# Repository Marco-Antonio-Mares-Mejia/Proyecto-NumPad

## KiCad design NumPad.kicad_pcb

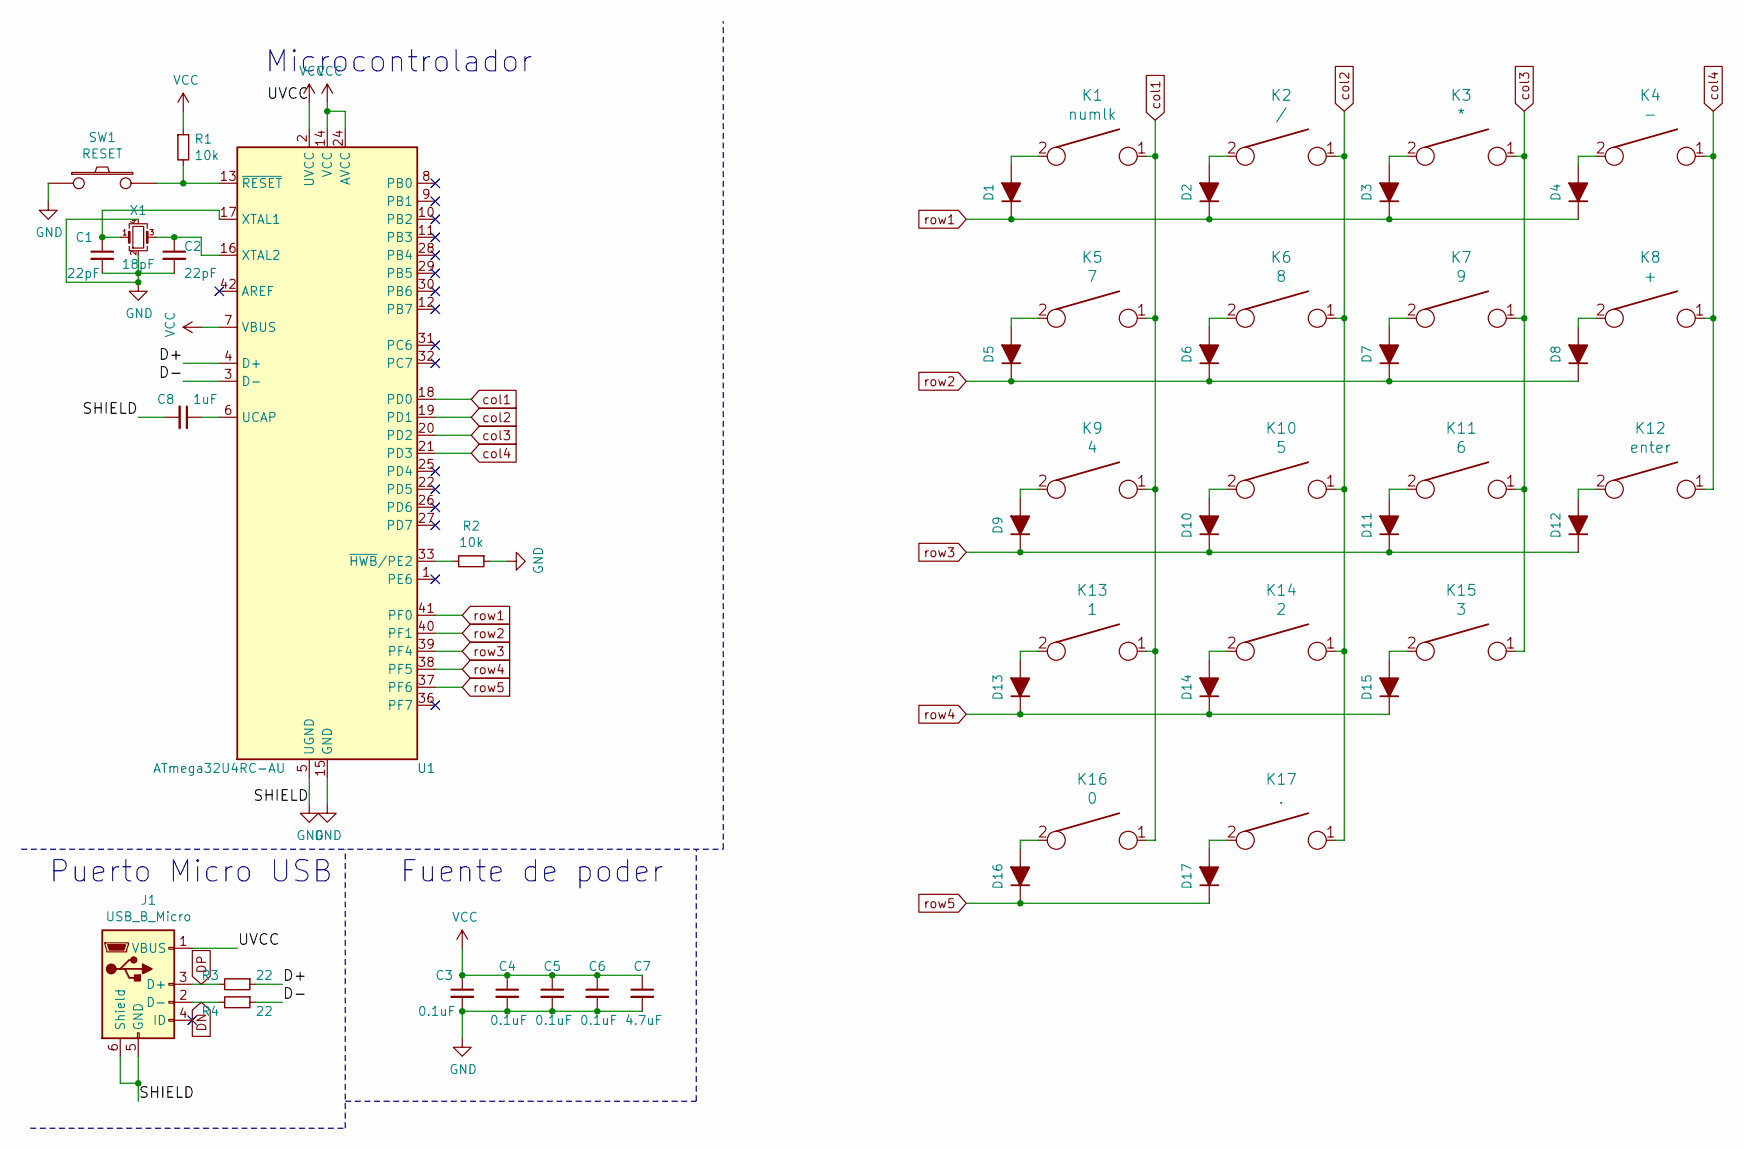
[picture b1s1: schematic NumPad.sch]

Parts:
C1, C2: 22pF; C_0805_2012Metric
C3, C4, C5, C6: 0.1uF; C_0805_2012Metric
C7: 4.7uF; C_0805_2012Metric
C8: 1uF; C_0805_2012Metric
D1, D2, D3, D4, D5, D6, D7, D8, D9, D10, D11, D12, D13, D14, D15, D16, D17: D_ALT; D_SOD-123
J1: USB_B_Micro; USB_microB
K1: numlk; SW_Cherry_MX_1.00u_PCB
K2: /; SW_Cherry_MX_1.00u_PCB
K3: *; SW_Cherry_MX_1.00u_PCB
K4: -; SW_Cherry_MX_1.00u_PCB
K5: 7; SW_Cherry_MX_1.00u_PCB
K6: 8; SW_Cherry_MX_1.00u_PCB
K7: 9; SW_Cherry_MX_1.00u_PCB
K8: +; SW_Cherry_MX_2.00u_Vertical_PCB
K9: 4; SW_Cherry_MX_1.00u_PCB
K10: 5; SW_Cherry_MX_1.00u_PCB
K11: 6; SW_Cherry_MX_1.00u_PCB
K12: enter; SW_Cherry_MX_2.00u_Vertical_PCB
K13: 1; SW_Cherry_MX_1.00u_PCB
K14: 2; SW_Cherry_MX_1.00u_PCB
K15: 3; SW_Cherry_MX_1.00u_PCB
K16: 0; SW_Cherry_MX_2.00u_PCB
K17: .; SW_Cherry_MX_1.00u_PCB
R1, R2: 10k; R_0805_2012Metric
R3, R4: 22; R_0603_1608Metric
SW1: RESET; SW_PUSH_6mm
U1: ATmega32U4RC-AU; TQFP-44_10x10mm_P0.8mm
X1: 18pF; Crystal_SMD_SeikoEpson_FA238-4Pin_3.2x2.5mm

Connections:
/D+: R3.1, U1.4 (D+)
/D-: R4.1, U1.3 (D-)
DN: J1.2 (D-), R4.2
DP: J1.3 (D+), R3.2
GND: C1.2, C2.2, C3.2, C4.2, C5.2, C6.2, C7.2, C8.2, J1.5 (GND), J1.6 (Shield), R2.1, SW1.1, U1.5 (UGND), U1.15 (GND), U1.23 (GND), U1.35 (GND), U1.43 (GND), X1.2, X1.4
unnamed: C1.1, U1.17 (XTAL1), X1.1
unnamed: C2.1, U1.16 (XTAL2), X1.3
unnamed: C8.1, U1.6 (UCAP)
unnamed: D1.2 (A), K1.2
unnamed: D2.2 (A), K2.2
unnamed: D3.2 (A), K3.2
unnamed: D4.2 (A), K4.2
unnamed: D5.2 (A), K5.2
unnamed: D6.2 (A), K6.2
unnamed: D7.2 (A), K7.2
unnamed: D8.2 (A), K8.2
unnamed: D9.2 (A), K9.2
unnamed: D10.2 (A), K10.2
unnamed: D11.2 (A), K11.2
unnamed: D12.2 (A), K12.2
unnamed: D13.2 (A), K13.2
unnamed: D14.2 (A), K14.2
unnamed: D15.2 (A), K15.2
unnamed: D16.2 (A), K16.2
unnamed: D17.2 (A), K17.2
unnamed: R1.2, SW1.2, U1.13 (~RESET)
unnamed: R2.2, U1.33 (~HWB~/PE2)
VCC: C3.1, C4.1, C5.1, C6.1, C7.1, J1.1 (VBUS), R1.1, U1.2 (UVCC), U1.7 (VBUS), U1.14 (VCC), U1.24 (AVCC), U1.34 (VCC), U1.44 (AVCC)
col1: K1.1, K5.1, K9.1, K13.1, K16.1, U1.18 (PD0)
col2: K2.1, K6.1, K10.1, K14.1, K17.1, U1.19 (PD1)
col3: K3.1, K7.1, K11.1, K15.1, U1.20 (PD2)
col4: K4.1, K8.1, K12.1, U1.21 (PD3)
row1: D1.1 (K), D2.1 (K), D3.1 (K), D4.1 (K), U1.41 (PF0)
row2: D5.1 (K), D6.1 (K), D7.1 (K), D8.1 (K), U1.40 (PF1)
row3: D9.1 (K), D10.1 (K), D11.1 (K), D12.1 (K), U1.39 (PF4)
row4: D13.1 (K), D14.1 (K), D15.1 (K), U1.38 (PF5)
row5: D16.1 (K), D17.1 (K), U1.37 (PF6)

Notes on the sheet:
Microcontrolador
Fuente de poder
Puerto Micro USB

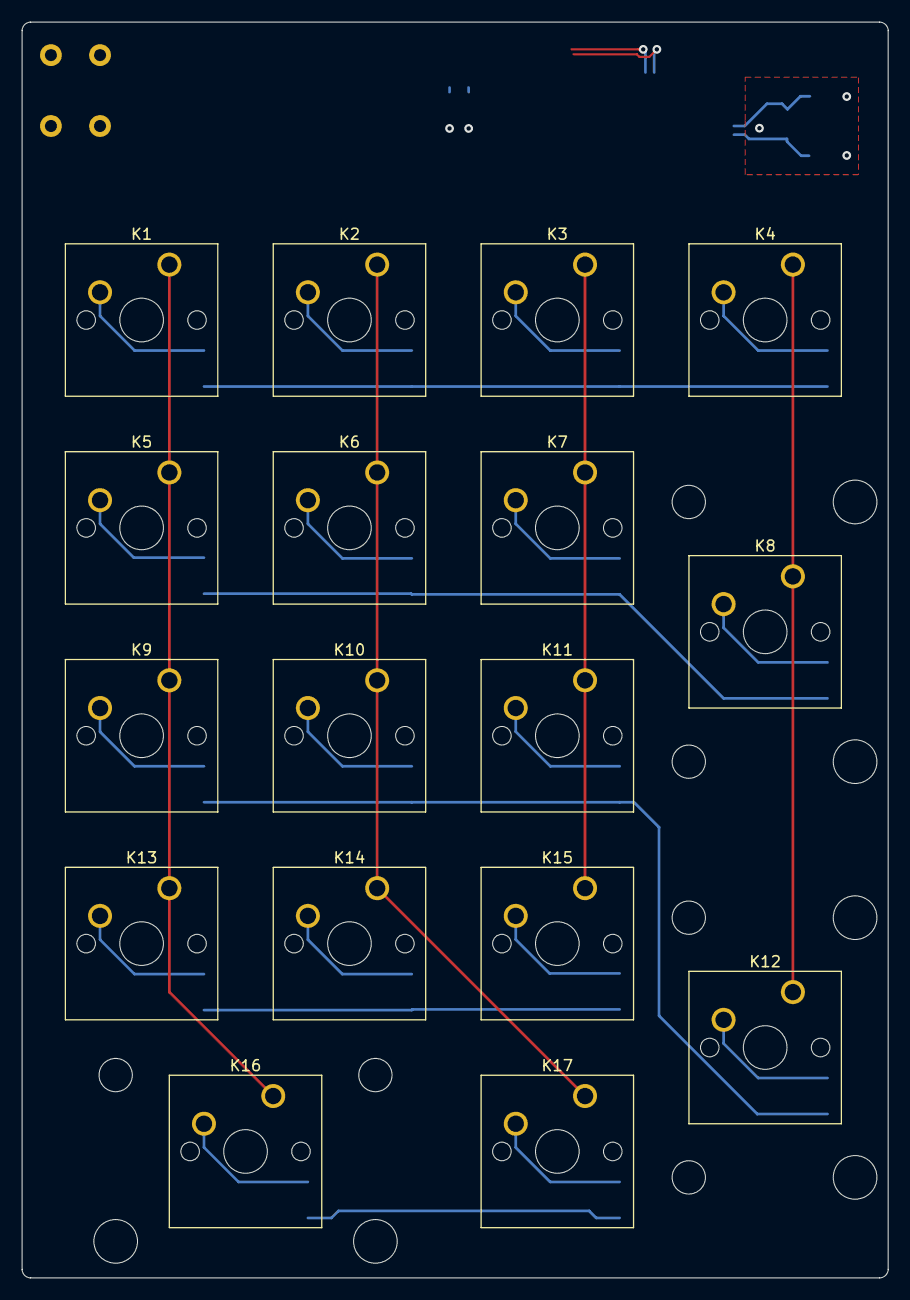
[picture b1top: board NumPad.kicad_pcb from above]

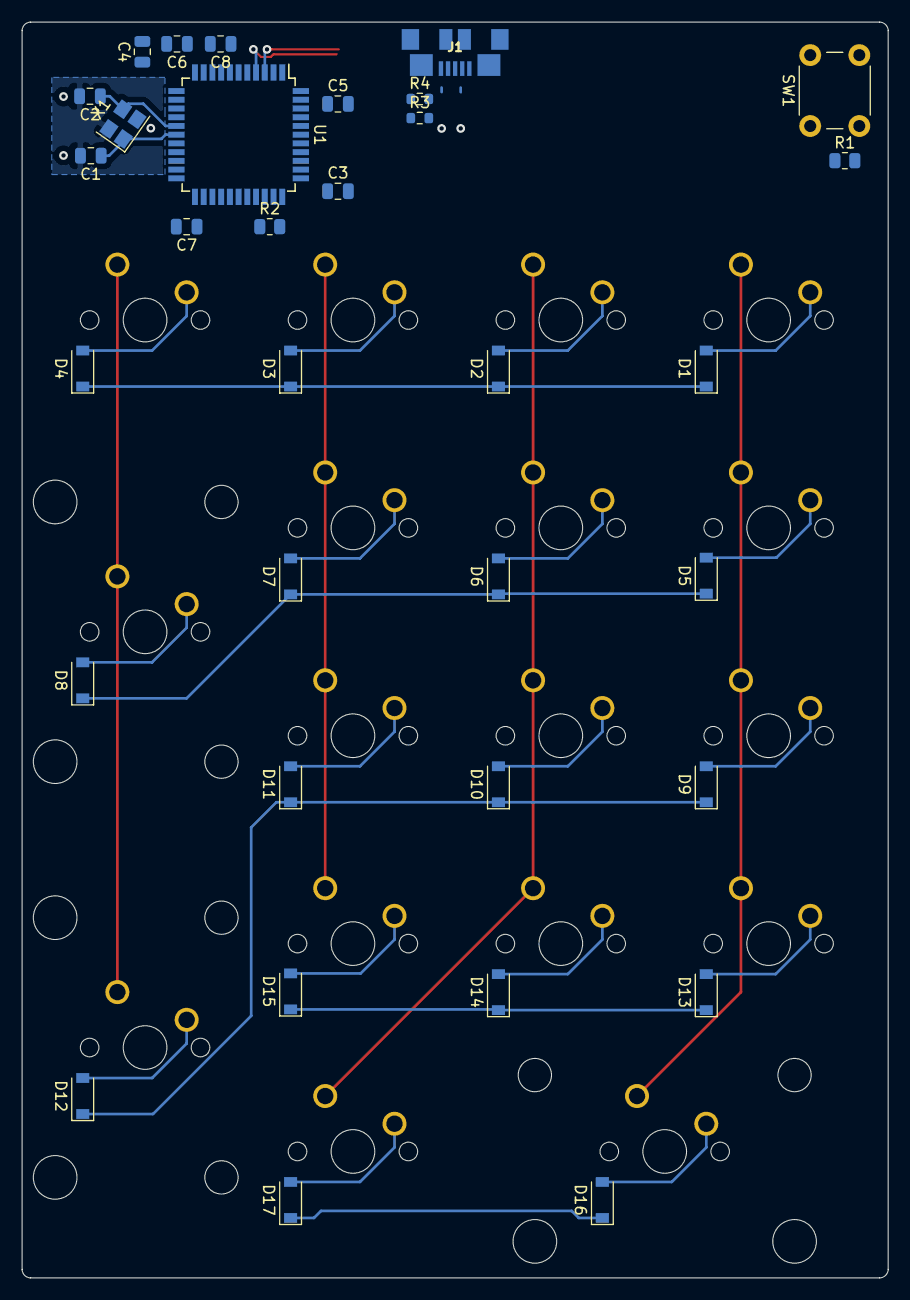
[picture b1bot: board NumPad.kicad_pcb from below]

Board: 2 copper layers, 79.4 x 115.1 mm, 50 parts (33 on the bottom side), 37 nets.

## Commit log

2021-07-07 Esquematico sin terminar
2021-07-12 Esquemático terminado y PCB empezada
2021-07-13 Edge cuts finalizados
2021-07-15 Planos de tierra y vcc añadidos
2021-07-16 Matriz de switches del esquemático arreglada
2021-07-16 Plugins añadidos y columnadas enrutadas
2021-07-20 Mas conexiones y correcion de errores.
